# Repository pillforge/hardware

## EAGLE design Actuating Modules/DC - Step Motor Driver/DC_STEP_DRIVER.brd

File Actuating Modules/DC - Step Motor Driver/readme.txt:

XXXXXXXXXXXXXXXXXXXXXXXXXXXXXXXXXXXXXXXXXXXXXXXXXXXXXXXXXXXXXXXXXXXXXXXXXXXXX
X                                                                           X
X   Artwork and documentation done by: STORM LAB                            X
X                                                                           X
X   Company: VANDERBILT UNIVERSITY                                          X
XXXXXXXXXXXXXXXXXXXXXXXXXXXXXXXXXXXXXXXXXXXXXXXXXXXXXXXXXXXXXXXXXXXXXXXXXXXXX

PROJECT : DC_STEP_DRIVER
PCB NAME : DC_STEP_DRIVER
REVISION: 1.1 
DATE: 4-28-2015

PCB DESCRIPTION: 2 LAYER PCB 0.8 MM NOMINAL THICKNESS FR4
		Dimensions in mil (0.001 inch)
                            DOUBLE SIDE SOLDER MASK,
                            DOUBLE SIDE SILKSCREEN,
                            6 MIL MIN TRACE WIDTH AND 6 MIL MIN ISOLATION
		Dielectric constant for FR4 is 4.5

FILE NAME            		DESCRIPTION                               	FILE TYPE
-------------------------------------------------------------------------------------------
***PCB MANUFACTURING FILES:
DC_STEP_DRIVER.cmp				LAYER 1 COMPONENT SIDE/POSITIV              EXT. GERBER
DC_STEP_DRIVER.sol				LAYER 2 Inner layer/POSITIV                 EXT. GERBER

DC_STEP_DRIVER.stc				SOLDER MASK COMPONENT SIDE/NEGATIVE         EXT. GERBER
DC_STEP_DRIVER.stl				SOLDER MASK SOLDER SIDE/NEGATIVE            EXT. GERBER

DC_STEP_DRIVER.plc				SILKSCREEN COMPONENT SIDE/POSITIVE          EXT. GERBER
DC_STEP_DRIVER.pls				SILKSCREEN SOLDER SIDE/POSITIVE             EXT. GERBER

DC_STEP_DRIVER.crc				SOLDER PAST COMPONENT SIDE/POSITIVE         EXT. GERBER
DC_STEP_DRIVER.crs				SOLDER PAST SOLDER SIDE/POSITIVE            EXT. GERBER

DC_STEP_DRIVER.drd				DRILL/MECHANICAL DRAWING                    EXT. GERBER
DC_STEP_DRIVER.dri				DRILL/NC DRILL REPORT                       ASCII
DC_STEP_DRIVER.dim				BOARD OUTLINE                      	    EXT. GERBER

DC_STEP_DRIVER_partlist.xls		        PART LIST				    ASCII

***PDF FILES:
DC_STEP_DRIVER.PDF	Circuit Diagram

***EAGLE  FILES:
DC_STEP_DRIVER.SCH			Eagle 6.6 Schematic file
DC_STEP_DRIVER.BRD			Eagle 6.6 Layout file

README.TXT              THIS FILE                                   ASCII

***REVISION HISTORY

none

END.

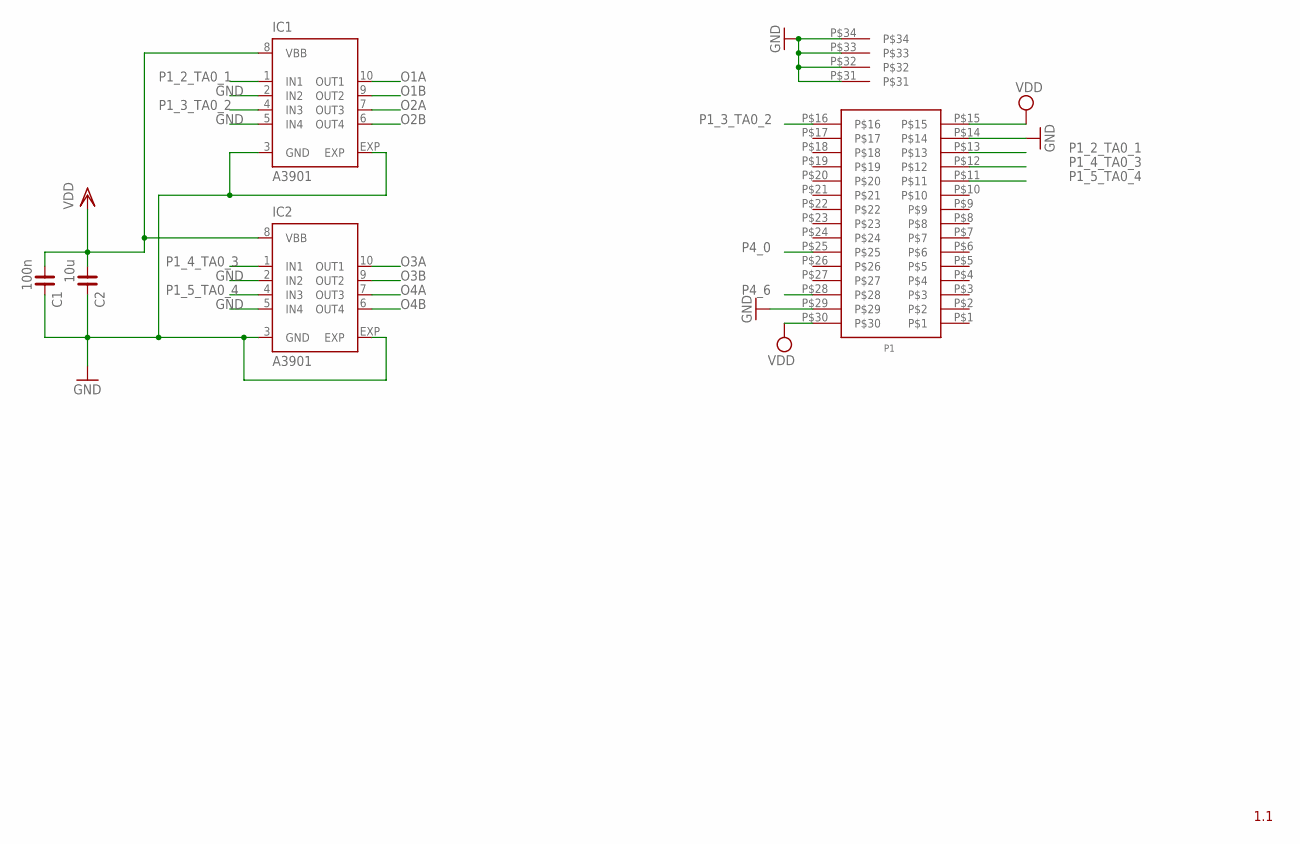
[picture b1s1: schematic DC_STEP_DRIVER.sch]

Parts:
C1: 100n; C0402
C2: 10u; C0402
IC1, IC2: A3901; DFN10-3X3
P1: 55909-0374; 55909-0374_PLUG

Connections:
GND: C1.2, C2.2, IC1.2 (IN2), IC1.3 (GND), IC1.5 (IN4), IC1.EXP, IC2.2 (IN2), IC2.3 (GND), IC2.5 (IN4), IC2.EXP, P1.P$14, P1.P$29, P1.P$31, P1.P$32, P1.P$33, P1.P$34
O1A: IC1.10 (OUT1)
O1B: IC1.9 (OUT2)
O2A: IC1.7 (OUT3)
O2B: IC1.6 (OUT4)
O3A: IC2.10 (OUT1)
O3B: IC2.9 (OUT2)
O4A: IC2.7 (OUT3)
O4B: IC2.6 (OUT4)
P1_2_TA0_1: IC1.1 (IN1), P1.P$13
P1_3_TA0_2: IC1.4 (IN3), P1.P$16
P1_4_TA0_3: IC2.1 (IN1), P1.P$12
P1_5_TA0_4: IC2.4 (IN3), P1.P$11
P4_0: P1.P$25
P4_6: P1.P$28
VDD: C1.1, C2.1, IC1.8 (VBB), IC2.8 (VBB), P1.P$15, P1.P$30

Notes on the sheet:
1.1

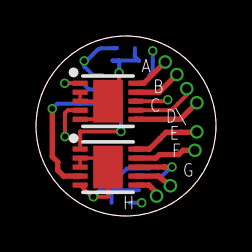
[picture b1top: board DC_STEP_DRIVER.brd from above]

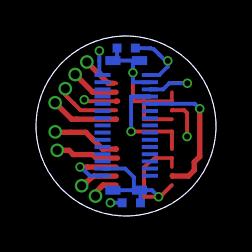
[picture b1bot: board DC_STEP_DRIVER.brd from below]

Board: 4 copper layers, 10.0 x 10.0 mm, 5 parts (3 on the bottom side), 6 nets.

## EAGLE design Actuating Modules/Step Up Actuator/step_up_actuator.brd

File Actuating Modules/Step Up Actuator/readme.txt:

XXXXXXXXXXXXXXXXXXXXXXXXXXXXXXXXXXXXXXXXXXXXXXXXXXXXXXXXXXXXXXXXXXXXXXXXXXXXX
X                                                                           X
X   Artwork and documentation done by: STORM LAB                            X
X                                                                           X
X   Company: VANDERBILT UNIVERSITY                                          X
XXXXXXXXXXXXXXXXXXXXXXXXXXXXXXXXXXXXXXXXXXXXXXXXXXXXXXXXXXXXXXXXXXXXXXXXXXXXX

PROJECT : step_up_actuator
PCB NAME : step_up_actuator
REVISION: 1.1 
DATE: 4-28-2015

PCB DESCRIPTION: 2 LAYER PCB 0.8 MM NOMINAL THICKNESS FR4
		Dimensions in mil (0.001 inch)
                            DOUBLE SIDE SOLDER MASK,
                            DOUBLE SIDE SILKSCREEN,
                            6 MIL MIN TRACE WIDTH AND 6 MIL MIN ISOLATION
		Dielectric constant for FR4 is 4.5

FILE NAME            		DESCRIPTION                               	FILE TYPE
-------------------------------------------------------------------------------------------
***PCB MANUFACTURING FILES:
step_up_actuator.cmp				LAYER 1 COMPONENT SIDE/POSITIV              EXT. GERBER
step_up_actuator.sol				LAYER 2 Inner layer/POSITIV                 EXT. GERBER

step_up_actuator.stc				SOLDER MASK COMPONENT SIDE/NEGATIVE         EXT. GERBER
step_up_actuator.stl				SOLDER MASK SOLDER SIDE/NEGATIVE            EXT. GERBER

step_up_actuator.plc				SILKSCREEN COMPONENT SIDE/POSITIVE          EXT. GERBER
step_up_actuator.pls				SILKSCREEN SOLDER SIDE/POSITIVE             EXT. GERBER

step_up_actuator.crc				SOLDER PAST COMPONENT SIDE/POSITIVE         EXT. GERBER
step_up_actuator.crs				SOLDER PAST SOLDER SIDE/POSITIVE            EXT. GERBER

step_up_actuator.drd				DRILL/MECHANICAL DRAWING                    EXT. GERBER
step_up_actuator.dri				DRILL/NC DRILL REPORT                       ASCII

step_up_actuator.dim				BOARD OUTLINE                      	    EXT. GERBER

step_up_actuator_partlist.xls		        PART LIST				    ASCII

***PDF FILES:
step_up_actuator.PDF	Circuit Diagram

***EAGLE  FILES:
step_up_actuator.SCH			Eagle 6.6 Schematic file
step_up_actuator.BRD			Eagle 6.6 Layout file

README.TXT              THIS FILE                                   ASCII

***REVISION HISTORY

none

END.

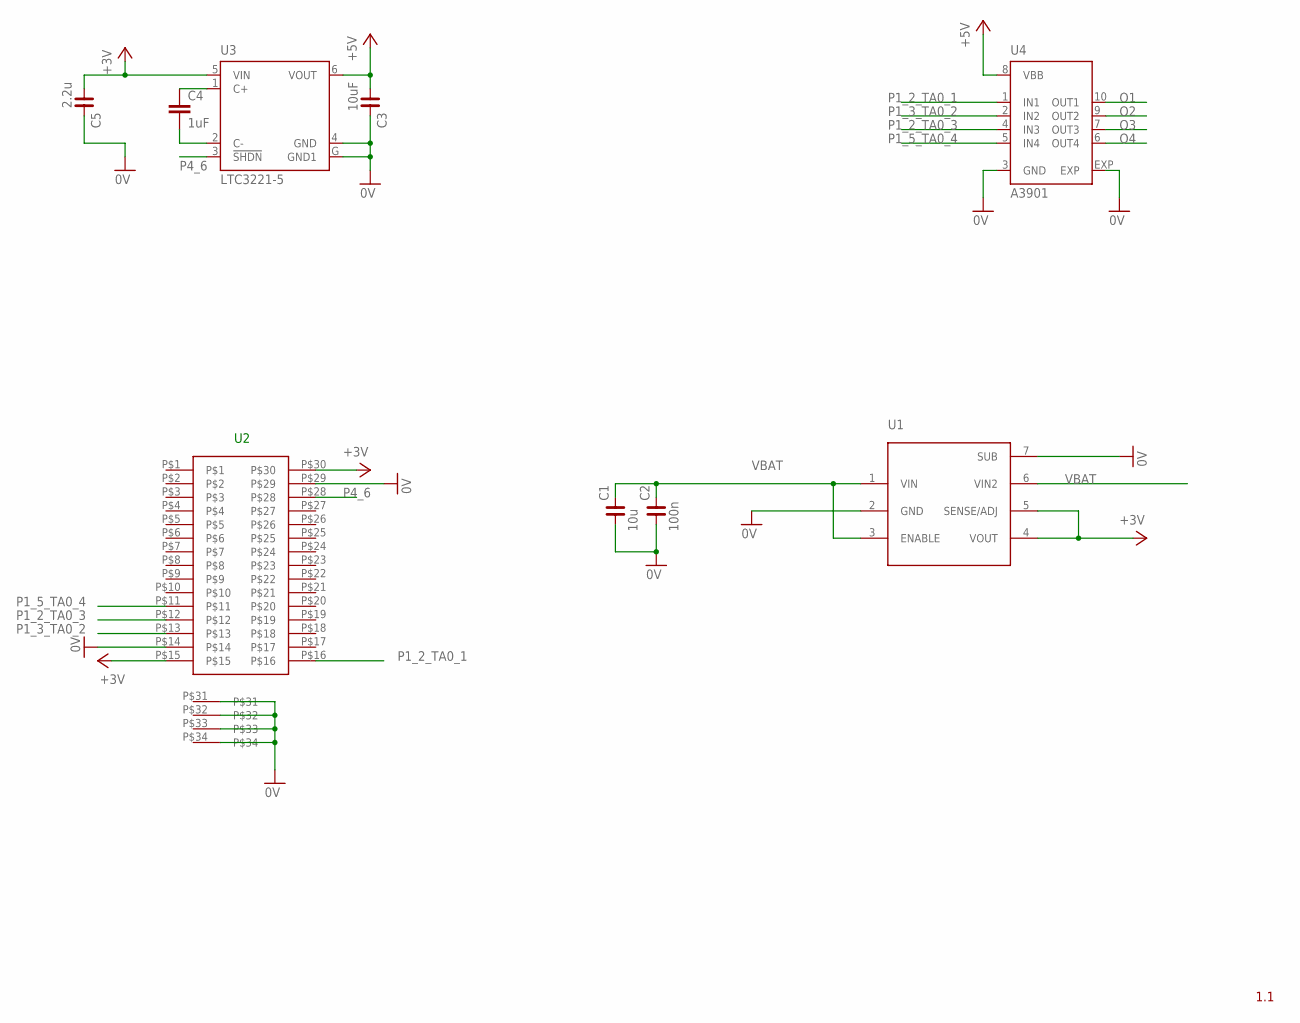
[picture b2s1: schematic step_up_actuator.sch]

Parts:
C1: 10u; C0402
C2: 100n; C0402
C3: 10uF; C1206
C4: 1uF; C0402
C5: 2.2u; C0402
U3: LTC3221-5; DFN6-2X2
U4: A3901; DFN10-3X3
U$1: NCP606
U$3: 51338-0374_RECEPTACLE

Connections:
0V: C1.1, C2.1, C3.2, C5.2, U3.4 (GND), U3.G (GND1), U4.3 (GND), U4.EXP, U$1.2 (GND), U$1.7 (SUB), U$3.P$14, U$3.P$29
+3V3: C5.1, U3.5 (VIN), U$1.4 (VOUT), U$1.5 (SENSE/ADJ), U$3.P$15, U$3.P$30
+5V: C3.1, U3.6 (VOUT), U4.8 (VBB)
unnamed: C4.1, U3.1 (C+)
unnamed: C4.2, U3.2 (C-)
O1: U4.10 (OUT1)
O2: U4.9 (OUT2)
O3: U4.7 (OUT3)
O4: U4.6 (OUT4)
P1_2_TA0_1: U4.1 (IN1), U$3.P$16
P1_2_TA0_3: U4.4 (IN3), U$3.P$12
P1_3_TA0_2: U4.2 (IN2), U$3.P$13
P1_5_TA0_4: U4.5 (IN4), U$3.P$11
P4_6: U3.3 (!SHDN), U$3.P$28
VBAT: C1.2, C2.2, U$1.1 (VIN), U$1.3 (ENABLE), U$1.6 (VIN2)

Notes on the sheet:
1.1

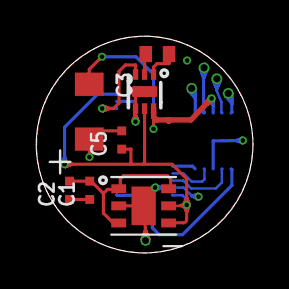
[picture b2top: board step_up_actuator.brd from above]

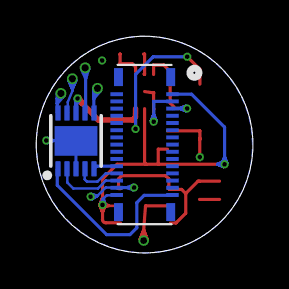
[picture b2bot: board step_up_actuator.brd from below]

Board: 4 copper layers, 12.0 x 12.0 mm, 9 parts (2 on the bottom side), 11 nets.

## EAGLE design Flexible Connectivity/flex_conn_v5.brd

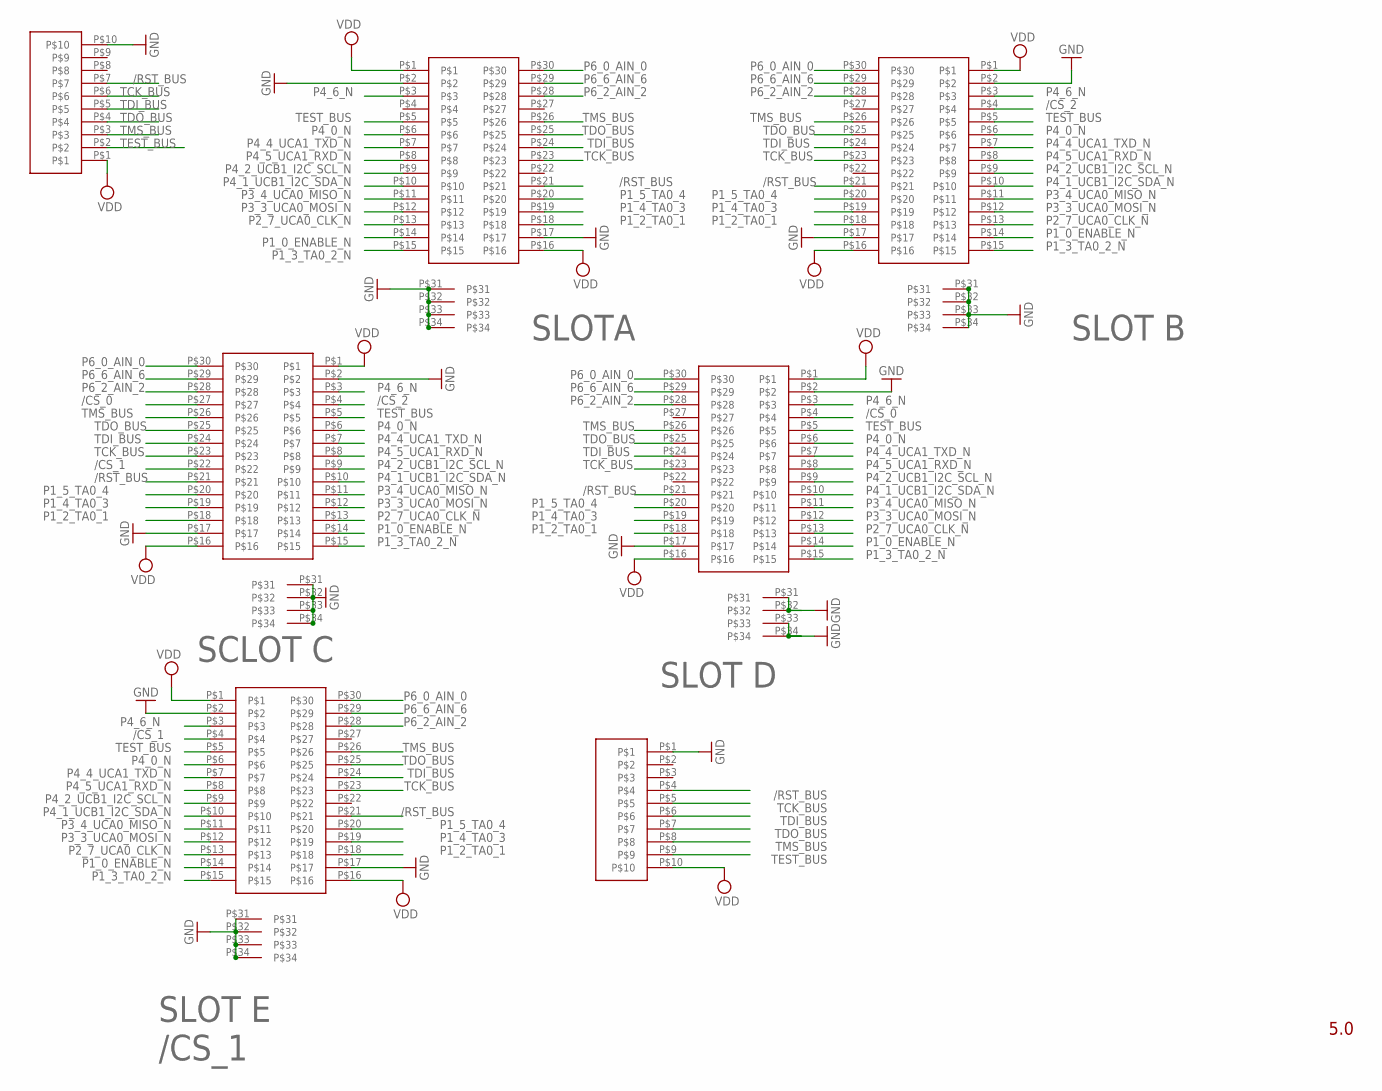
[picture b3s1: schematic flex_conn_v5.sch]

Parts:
U$1, U$2, U$3, U$4, U$6: 500913-0302_REC_30CONN_2
U$5, U$7: CABLE_ADAPTATOR; FPC_FFC

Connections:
/CS_0: U$1.P$4, U$6.P$27
/CS_1: U$4.P$4, U$6.P$22
/CS_2: U$2.P$4, U$6.P$4
/RST_BUS: U$1.P$21, U$2.P$21, U$3.P$21, U$4.P$21, U$5.P$7, U$6.P$21, U$7.P$4
GND: U$1.P$2, U$1.P$17, U$1.P$31, U$1.P$32, U$1.P$33, U$1.P$34, U$2.P$2, U$2.P$17, U$2.P$31, U$2.P$32, U$2.P$33, U$2.P$34, U$3.P$2, U$3.P$17, U$3.P$31, U$3.P$32, U$3.P$33, U$3.P$34, U$4.P$2, U$4.P$17, U$4.P$31, U$4.P$32, U$4.P$33, U$4.P$34, U$5.P$10, U$6.P$2, U$6.P$17, U$6.P$31, U$6.P$32, U$6.P$33, U$6.P$34, U$7.P$1
P1_0_ENABLE_N: U$1.P$14, U$2.P$14, U$3.P$14, U$4.P$14, U$6.P$14
P1_2_TA0_1: U$1.P$18, U$2.P$18, U$3.P$18, U$4.P$18, U$6.P$18
P1_3_TA0_2_N: U$1.P$15, U$2.P$15, U$3.P$15, U$4.P$15, U$6.P$15
P1_4_TA0_3: U$1.P$19, U$2.P$19, U$3.P$19, U$4.P$19, U$6.P$19
P1_5_TA0_4: U$1.P$20, U$2.P$20, U$3.P$20, U$4.P$20, U$6.P$20
P2_7_UCA0_CLK_N: U$1.P$13, U$2.P$13, U$3.P$13, U$4.P$13, U$6.P$13
P3_3_UCA0_MOSI_N: U$1.P$12, U$2.P$12, U$3.P$12, U$4.P$12, U$6.P$12
P3_4_UCA0_MISO_N: U$1.P$11, U$2.P$11, U$3.P$11, U$4.P$11, U$6.P$11
P4_0_N: U$1.P$6, U$2.P$6, U$3.P$6, U$4.P$6, U$6.P$6
P4_1_UCB1_I2C_SDA_N: U$1.P$10, U$2.P$10, U$3.P$10, U$4.P$10, U$6.P$10
P4_2_UCB1_I2C_SCL_N: U$1.P$9, U$2.P$9, U$3.P$9, U$4.P$9, U$6.P$9
P4_4_UCA1_TXD_N: U$1.P$7, U$2.P$7, U$3.P$7, U$4.P$7, U$6.P$7
P4_5_UCA1_RXD_N: U$1.P$8, U$2.P$8, U$3.P$8, U$4.P$8, U$6.P$8
P4_6_N: U$1.P$3, U$2.P$3, U$3.P$3, U$4.P$3, U$6.P$3
P6_0_AIN_0: U$1.P$30, U$2.P$30, U$3.P$30, U$4.P$30, U$6.P$30
P6_2_AIN_2: U$1.P$28, U$2.P$28, U$3.P$28, U$4.P$28, U$6.P$28
P6_6_AIN_6: U$1.P$29, U$2.P$29, U$3.P$29, U$4.P$29, U$6.P$29
TCK_BUS: U$1.P$23, U$2.P$23, U$3.P$23, U$4.P$23, U$5.P$6, U$6.P$23, U$7.P$5
TDI_BUS: U$1.P$24, U$2.P$24, U$3.P$24, U$4.P$24, U$5.P$5, U$6.P$24, U$7.P$6
TDO_BUS: U$1.P$25, U$2.P$25, U$3.P$25, U$4.P$25, U$5.P$4, U$6.P$25, U$7.P$7
TEST_BUS: U$1.P$5, U$2.P$5, U$3.P$5, U$4.P$5, U$5.P$2, U$6.P$5, U$7.P$9
TMS_BUS: U$1.P$26, U$2.P$26, U$3.P$26, U$4.P$26, U$5.P$3, U$6.P$26, U$7.P$8
VDD: U$1.P$1, U$1.P$16, U$2.P$1, U$2.P$16, U$3.P$1, U$3.P$16, U$4.P$1, U$4.P$16, U$5.P$1, U$6.P$1, U$6.P$16, U$7.P$10

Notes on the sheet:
SLOTA
SLOT B
SCLOT C
SLOT D
SLOT E
/CS_1
5.0

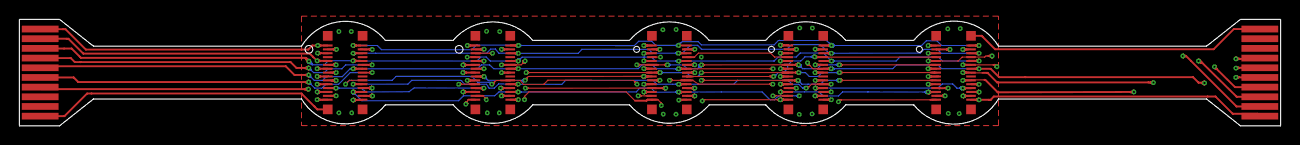
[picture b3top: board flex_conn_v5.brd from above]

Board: 4 copper layers, 130.3 x 11.0 mm, 7 parts (0 on the bottom side), 28 nets.

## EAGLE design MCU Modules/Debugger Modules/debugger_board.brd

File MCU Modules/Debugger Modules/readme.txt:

XXXXXXXXXXXXXXXXXXXXXXXXXXXXXXXXXXXXXXXXXXXXXXXXXXXXXXXXXXXXXXXXXXXXXXXXXXXXX
X                                                                           X
X   Artwork and documentation done by: STORM LAB                            X
X                                                                           X
X   Company: VANDERBILT UNIVERSITY                                          X
XXXXXXXXXXXXXXXXXXXXXXXXXXXXXXXXXXXXXXXXXXXXXXXXXXXXXXXXXXXXXXXXXXXXXXXXXXXXX

PROJECT : debugger_board
PCB NAME : debugger_board
REVISION: 1.1 
DATE: 4-28-2015

PCB DESCRIPTION: 2 LAYER PCB 0.8 MM NOMINAL THICKNESS FR4
		Dimensions in mil (0.001 inch)
                            DOUBLE SIDE SOLDER MASK,
                            DOUBLE SIDE SILKSCREEN,
                            6 MIL MIN TRACE WIDTH AND 6 MIL MIN ISOLATION
		Dielectric constant for FR4 is 4.5

FILE NAME            		DESCRIPTION                               	FILE TYPE
-------------------------------------------------------------------------------------------
***PCB MANUFACTURING FILES:
debugger_board.cmp				LAYER 1 COMPONENT SIDE/POSITIV              EXT. GERBER
debugger_board.sol				LAYER 2 Inner layer/POSITIV                 EXT. GERBER

debugger_board.stc				SOLDER MASK COMPONENT SIDE/NEGATIVE         EXT. GERBER
debugger_board.stl				SOLDER MASK SOLDER SIDE/NEGATIVE            EXT. GERBER

debugger_board.plc				SILKSCREEN COMPONENT SIDE/POSITIVE          EXT. GERBER
debugger_board.pls				SILKSCREEN SOLDER SIDE/POSITIVE             EXT. GERBER

debugger_board.crc				SOLDER PAST COMPONENT SIDE/POSITIVE         EXT. GERBER
debugger_board.crs				SOLDER PAST SOLDER SIDE/POSITIVE            EXT. GERBER

debugger_board.drd				DRILL/MECHANICAL DRAWING                    EXT. GERBER
debugger_board.dri				DRILL/NC DRILL REPORT                       ASCII

debugger_board.dim				BOARD OUTLINE                      	    EXT. GERBER

debugger_board_partlist.xls		        PART LIST				    ASCII

***PDF FILES:
debugger_board.PDF	Circuit Diagram

***EAGLE  FILES:
debugger_board.SCH			Eagle 6.6 Schematic file
debugger_board.BRD			Eagle 6.6 Layout file

README.TXT              THIS FILE                                   ASCII

***REVISION HISTORY

none

END.

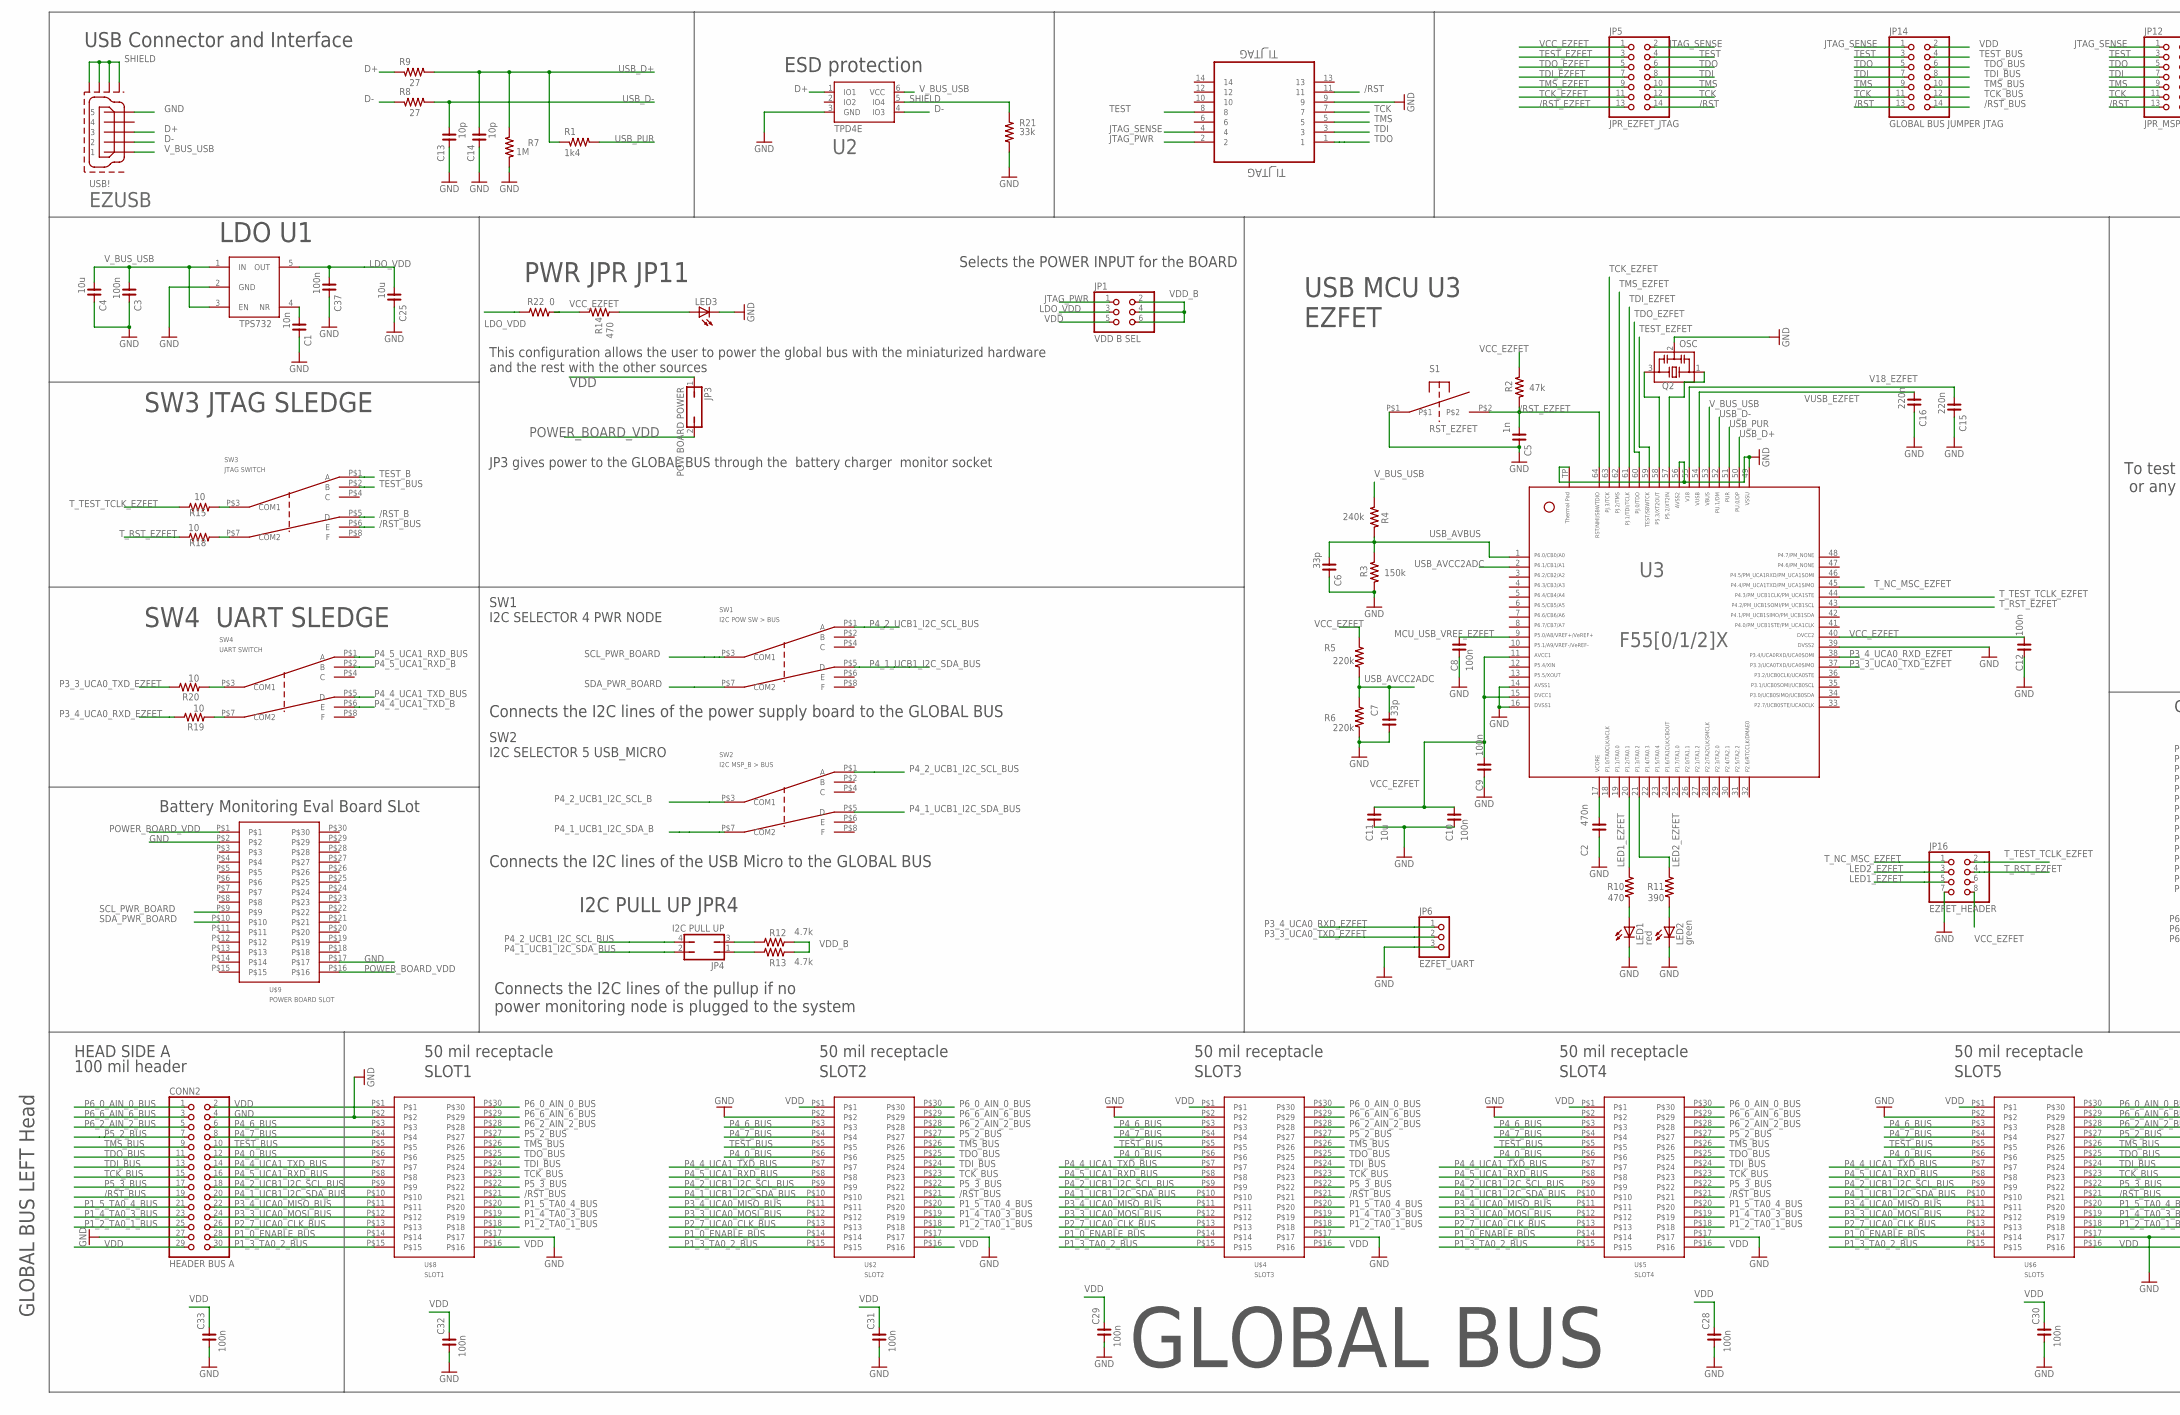
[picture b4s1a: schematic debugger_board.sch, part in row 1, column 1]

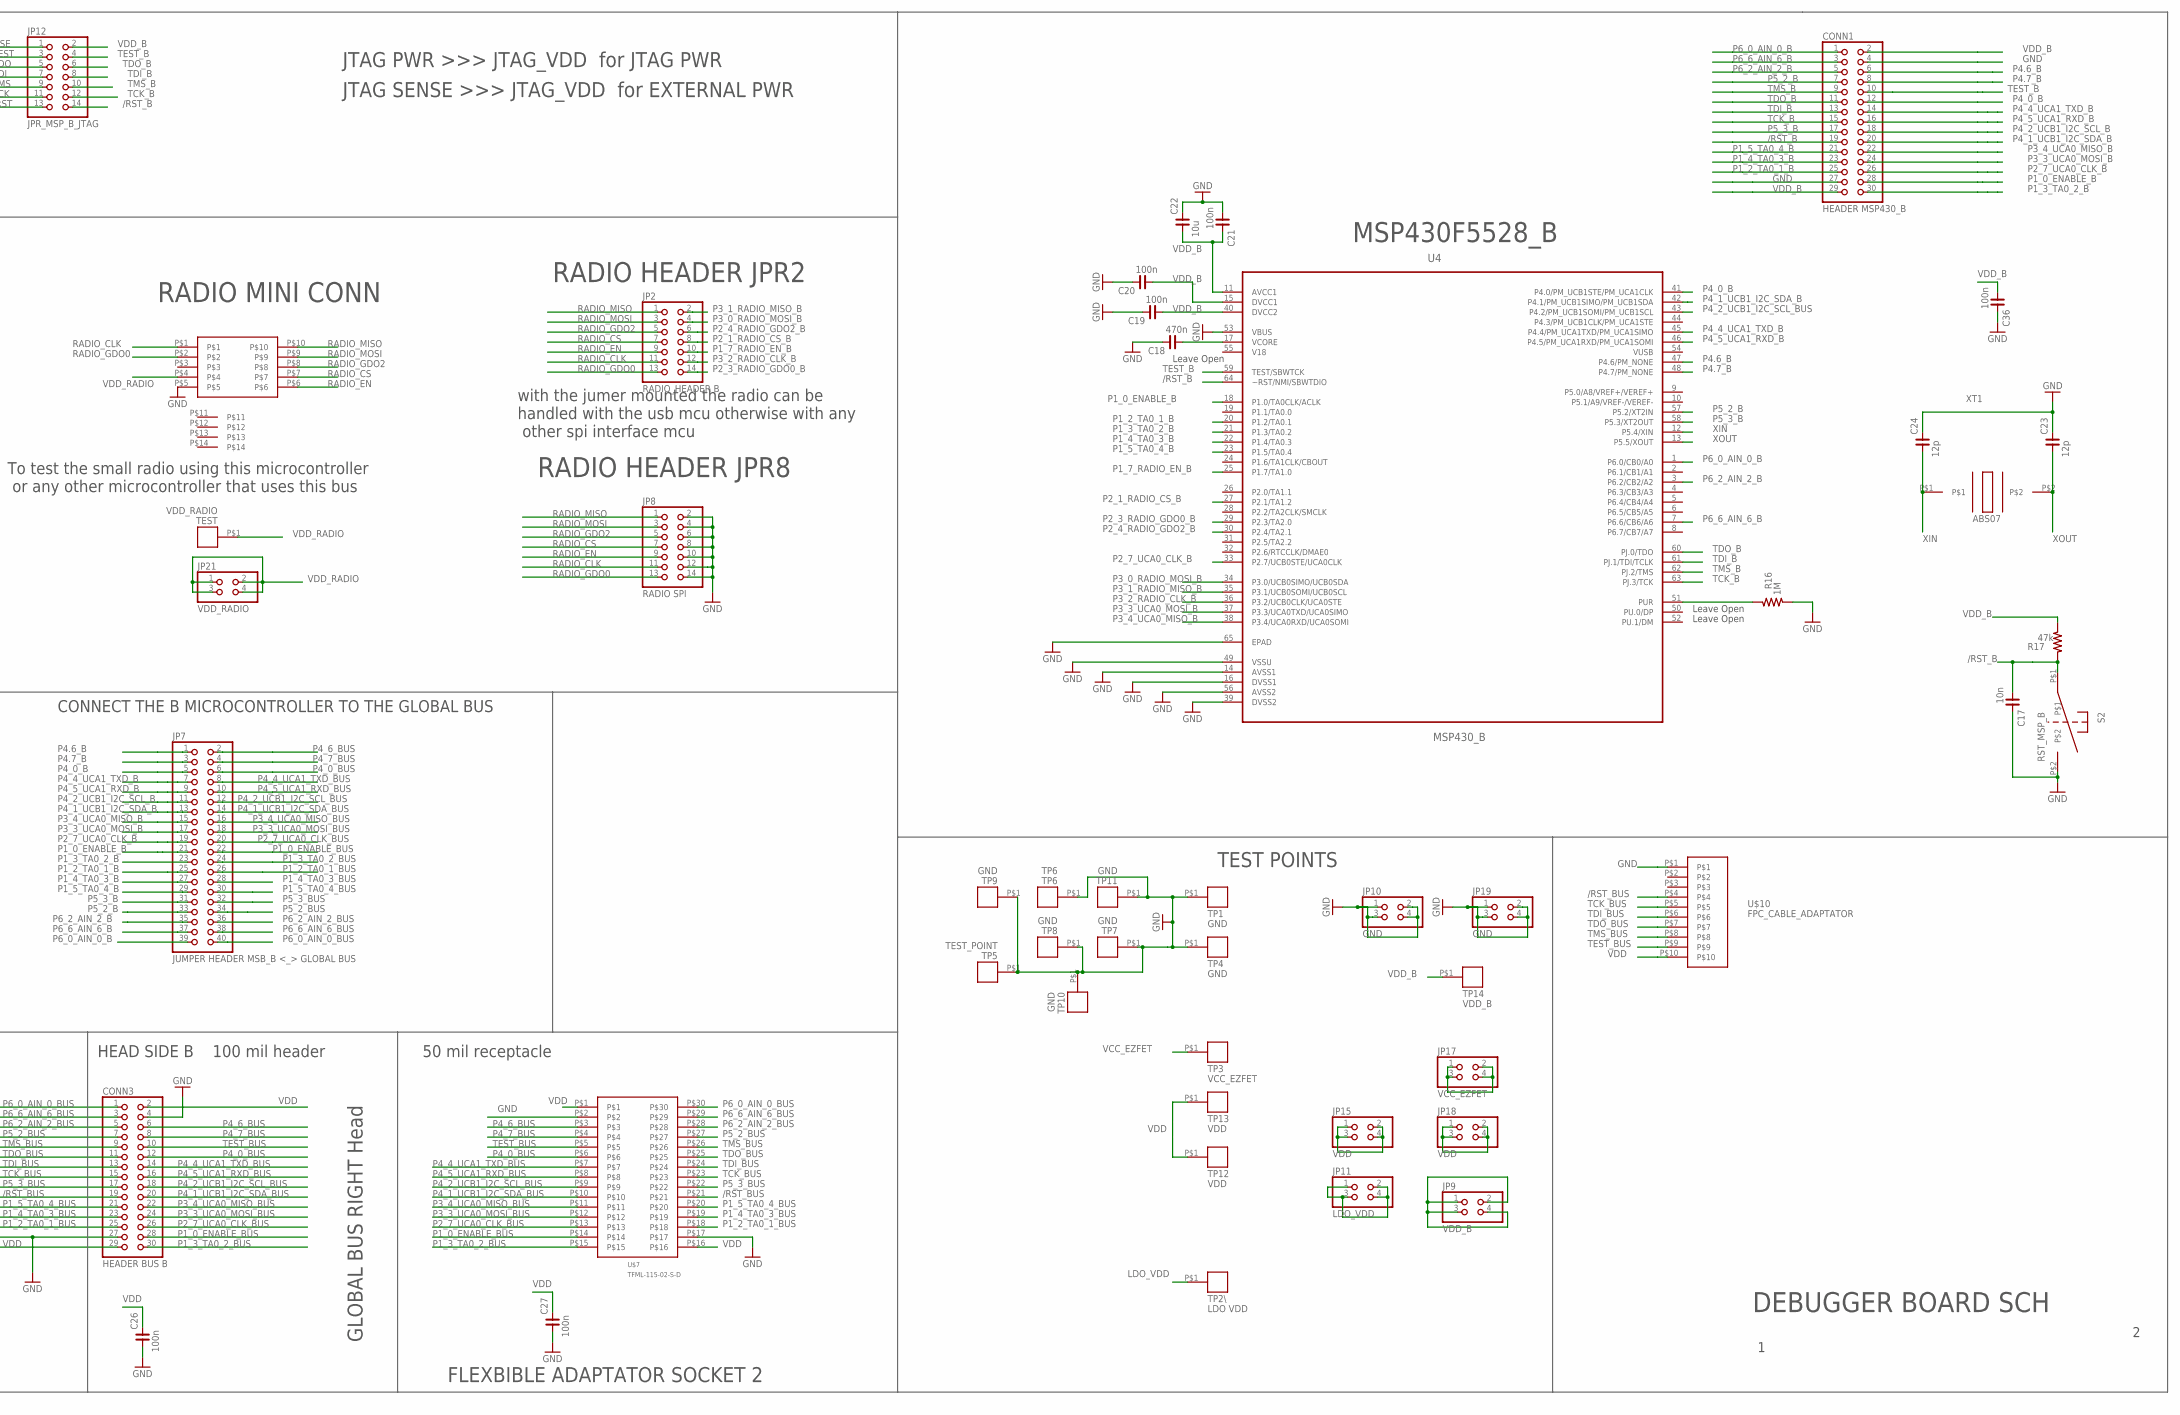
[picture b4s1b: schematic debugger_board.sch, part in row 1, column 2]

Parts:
C1, C17: 10n; C0603
C2, C18: 470n; C0603
C3, C8, C9, C10, C12, C19, C20, C21, C26, C27, C28, C29, C30, C31, C32, C33, C36, C37: 100n; C0603
C4, C11, C22, C25: 10u; C0603
C5: 1n; C0603
C6, C7: 33p; C0603
C13, C14: 10p; C0603
C15, C16: 220n; C0603
C23, C24: 12p; C0603
CONN1: HEADER MSP430_B; 2X15
CONN2: HEADER BUS A; 2X15
CONN3: HEADER BUS B; 2X15
EZUSB: USB!; UX60A-MB-5ST
JP1: VDD B SEL; 2X03
JP2: RADIO_HEADER B; 2X07
JP3: POW BOARD POWER; JP1
JP4: I2C PULL UP; JP2Q
JP5: JPR_EZFET_JTAG; 2X07
JP6: EZFET_UART; 1X03
JP7: JUMPER HEADER MSB_B <_> GLOBAL BUS; 2X20
JP8: RADIO SPI; 2X07
JP9: VDD_B; 2X02
JP10, JP19: GND; 2X02
JP11: LDO_VDD; 2X02
JP12: JPR_MSP_B_JTAG; 2X07
JP14: GLOBAL BUS JUMPER JTAG; 2X07
JP15, JP18: VDD; 2X02
JP16: EZFET_HEADER; 2X04
JP17: VCC_EZFET; 2X02
JP21: VDD_RADIO; 2X02
LED1: red; CHIP-LED0603
LED2: green; CHIP-LED0603
LED3: LEDCHIP-LED0603; CHIP-LED0603
Q2: OSC; CSTCR6M
R1: 1k4; R0603
R2, R17: 47k; R0603
R3: 150k; R0603
R4: 240k; R0603
R5, R6: 220k; R0603
R7, R16: 1M; R0603
R8, R9: 27; R0603
R10, R14: 470; R0603
R11: 390; R0603
R12, R13: 4.7k; R0603
R15, R18, R19, R20: 10; R0603
R21: 33k; R0603
R22: 0; R1206
RADIO_CONN: RADIO; 559099872_2X5_PLUG
S1: RST_EZFET; EVQ_11_TH
S2: RST_MSP_B; EVQ_11_TH
SW1: I2C POW SW > BUS; CL-SB-23B-02
SW2: I2C MSP_B > BUS; CL-SB-23B-02
SW3: JTAG SWITCH; CL-SB-23B-02
SW4: UART SWITCH; CL-SB-23B-02
TEST: VDD_RADIO; 5019_PAD
TI_JTAG: TI_JTAG; TYCO_5103308-2
TP1, TP4, TP7, TP8, TP9, TP10, TP11: GND; 5019_PAD
TP2\: LDO VDD; 5019_PAD
TP3: VCC_EZFET; 5019_PAD
TP5: TEST_POINT; 5019_PAD
TP6: TP6; 5019_PAD
TP12, TP13: VDD; 5019_PAD
TP14: VDD_B; 5019_PAD
U1: TPS73233; SOT23
U2: TPD4E; SON(DRY)6
U3: USB_EZFET; RGC64
U4: MSP430_B; QFN50P900X900X100-65N
U$2: SLOT2; TFML-115-02-S-D
U$4: SLOT3; TFML-115-02-S-D
U$5: SLOT4; TFML-115-02-S-D
U$6: SLOT5; TFML-115-02-S-D
U$7: TFML-115-02-S-D
U$8: SLOT1; TFML-115-02-S-D
U$9: POWER BOARD SLOT; TFML-115-02-S-D
U$10: FPC_CABLE_ADAPTATOR; FPC_FFC
U$16: OSC32K; ABS07

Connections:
/RST: JP5.14, JP12.13, JP14.13, TI_JTAG.11
/RST_B: C17.1, CONN1.19, JP12.14, R17.1, S2.P$1, SW3.P$5 (D), U4.64 (~RST/NMI/SBWTDIO)
/RST_BUS: CONN2.19, CONN3.19, JP14.14, SW3.P$6 (E), U$2.P$21, U$4.P$21, U$5.P$21, U$6.P$21, U$7.P$21, U$8.P$21, U$10.P$4
/RST_EZFET: C5.1, JP5.13, R2.1, S1.P$2, U3.64
D+: EZUSB.3, R9.1, U2.1 (IO1)
D-: EZUSB.2, R8.1, U2.4 (IO3)
GND: C1.2, C2.2, C3.2, C4.2, C5.2, C6.2, C7.1, C8.1, C9.1, C10.1, C11.1, C12.1, C13.2, C14.2, C15.2, C16.2, C17.2, C18.2, C19.2, C20.2, C21.1, C22.2, C23.2, C24.2, C25.2, C26.1, C27.1, C28.1, C29.1, C30.1, C31.1, C32.1, C33.1, C36.2, C37.2, CONN1.4, CONN1.27, CONN2.4, CONN2.27, CONN3.4, CONN3.27, EZUSB.5, JP6.3, JP8.2, JP8.4, JP8.6, JP8.8, JP8.10, JP8.12, JP8.14, JP10.1, JP10.2, JP10.3, JP10.4, JP16.7, JP19.1, JP19.2, JP19.3, JP19.4, LED1.C, LED2.C, LED3.C, Q2.2, R3.1, R6.2, R7.2, R16.2, R21.2, RADIO_CONN.P$5, S1.P$1, S2.P$2, TI_JTAG.9, TP1.P$1, TP4.P$1, TP5.P$1, TP6.P$1, TP7.P$1, TP8.P$1, TP9.P$1, TP10.P$1, TP11.P$1, U1.2 (GND), U2.3 (GND), U3.14, U3.16, U3.39, U3.49, U3.56, U3.TP, U4.14 (AVSS1), U4.16 (DVSS1), U4.39 (DVSS2), U4.49 (VSSU), U4.53 (VBUS), U4.56 (AVSS2), U4.65 (EPAD), U$2.P$2, U$2.P$17, U$4.P$2, U$4.P$17, U$5.P$2, U$5.P$17, U$6.P$2, U$6.P$17, U$7.P$2, U$7.P$17, U$8.P$2, U$8.P$17, U$9.P$2, U$9.P$17, U$10.P$1
JTAG_PWR: JP1.1, TI_JTAG.2
JTAG_SENSE: JP5.2, JP12.1, JP14.1, TI_JTAG.4
LDO_VDD: C25.1, C37.1, JP1.3, JP11.1, JP11.2, JP11.3, JP11.4, R22.2, TP2\.P$1, U1.5 (OUT)
LED1_EZFET: JP16.5, R10.2, U3.20
LED2_EZFET: JP16.3, R11.2, U3.21
MCU_USB_VREF_EZFET: C8.2, U3.9
unnamed: C18.1, U4.17 (VCORE)
unnamed: R16.1, U4.51 (PUR)
unnamed: JP4.1, R13.1
unnamed: C1.1, U1.4 (NR)
unnamed: Q2.3, U3.58
unnamed: Q2.1, U3.57
unnamed: C2.1, U3.17
unnamed: LED3.A, R14.1
unnamed: LED1.A, R10.1
unnamed: LED2.A, R11.1
unnamed: JP4.3, R12.1
unnamed: R15.1, SW3.P$3 (COM1)
unnamed: R18.2, SW3.P$7 (COM2)
unnamed: R20.1, SW4.P$3 (COM1)
unnamed: R19.1, SW4.P$7 (COM2)
P1_0_ENABLE_B: CONN1.28, JP7.21, U4.18 (P1.0/TA0CLK/ACLK)
P1_0_ENABLE_BUS: CONN2.28, CONN3.28, JP7.22, U$2.P$14, U$4.P$14, U$5.P$14, U$6.P$14, U$7.P$14, U$8.P$14
P1_2_TA0_1_B: CONN1.25, JP7.25, U4.20 (P1.2/TA0.1)
P1_2_TA0_1_BUS: CONN2.25, CONN3.25, JP7.26, U$2.P$18, U$4.P$18, U$5.P$18, U$6.P$18, U$7.P$18, U$8.P$18
P1_3_TA0_2_B: CONN1.30, JP7.23, U4.21 (P1.3/TA0.2)
P1_3_TA0_2_BUS: CONN2.30, CONN3.30, JP7.24, U$2.P$15, U$4.P$15, U$5.P$15, U$6.P$15, U$7.P$15, U$8.P$15
P1_4_TA0_3_B: CONN1.23, JP7.27, U4.22 (P1.4/TA0.3)
P1_4_TA0_3_BUS: CONN2.23, CONN3.23, JP7.28, U$2.P$19, U$4.P$19, U$5.P$19, U$6.P$19, U$7.P$19, U$8.P$19
P1_5_TA0_4_B: CONN1.21, JP7.29, U4.23 (P1.5/TA0.4)
P1_5_TA0_4_BUS: CONN2.21, CONN3.21, JP7.30, U$2.P$20, U$4.P$20, U$5.P$20, U$6.P$20, U$7.P$20, U$8.P$20
P1_7_RADIO_EN_B: JP2.10, U4.25 (P1.7/TA1.0)
P2_1_RADIO_CS_B: JP2.8, U4.27 (P2.1/TA1.2)
P2_3_RADIO_GDO0_B: JP2.14, U4.29 (P2.3/TA2.0)
P2_4_RADIO_GDO2_B: JP2.6, U4.30 (P2.4/TA2.1)
P2_7_UCA0_CLK_B: CONN1.26, JP7.19, U4.33 (P2.7/UCB0STE/UCA0CLK)
P2_7_UCA0_CLK_BUS: CONN2.26, CONN3.26, JP7.20, U$2.P$13, U$4.P$13, U$5.P$13, U$6.P$13, U$7.P$13, U$8.P$13
P3_0_RADIO_MOSI_B: JP2.4, U4.34 (P3.0/UCB0SIMO/UCB0SDA)
P3_1_RADIO_MISO_B: JP2.2, U4.35 (P3.1/UCB0SOMI/UCB0SCL)
P3_2_RADIO_CLK_B: JP2.12, U4.36 (P3.2/UCB0CLK/UCA0STE)
P3_3_UCA0_MOSI_B: CONN1.24, JP7.17, U4.37 (P3.3/UCA0TXD/UCA0SIMO)
P3_3_UCA0_MOSI_BUS: CONN2.24, CONN3.24, JP7.18, U$2.P$12, U$4.P$12, U$5.P$12, U$6.P$12, U$7.P$12, U$8.P$12
P3_3_UCA0_TXD_EZFET: JP6.2, R20.2, U3.37
P3_4_UCA0_MISO_B: CONN1.22, JP7.15, U4.38 (P3.4/UCA0RXD/UCA0SOMI)
P3_4_UCA0_MISO_BUS: CONN2.22, CONN3.22, JP7.16, U$2.P$11, U$4.P$11, U$5.P$11, U$6.P$11, U$7.P$11, U$8.P$11
P3_4_UCA0_RXD_EZFET: JP6.1, R19.2, U3.38
P4.6_B: CONN1.6, JP7.1, U4.47 (P4.6/PM_NONE)
P4.7_B: CONN1.8, JP7.3, U4.48 (P4.7/PM_NONE)
P4_0_B: CONN1.12, JP7.5, U4.41 (P4.0/PM_UCB1STE/PM_UCA1CLK)
P4_0_BUS: CONN2.12, CONN3.12, JP7.6, U$2.P$6, U$4.P$6, U$5.P$6, U$6.P$6, U$7.P$6, U$8.P$6
P4_1_UCB1_I2C_SDA_B: CONN1.20, JP7.13, SW2.P$7 (COM2), U4.42 (P4.1/PM_UCB1SIMO/PM_UCB1SDA)
P4_1_UCB1_I2C_SDA_BUS: CONN2.20, CONN3.20, JP4.2, JP7.14, SW1.P$5 (D), SW2.P$5 (D), U$2.P$10, U$4.P$10, U$5.P$10, U$6.P$10, U$7.P$10, U$8.P$10
P4_2_UCB1_I2C_SCL_B: CONN1.18, JP7.11, SW2.P$3 (COM1)
P4_2_UCB1_I2C_SCL_BUS: CONN2.18, CONN3.18, JP4.4, JP7.12, SW1.P$1 (A), SW2.P$1 (A), U4.43 (P4.2/PM_UCB1SOMI/PM_UCB1SCL), U$2.P$9, U$4.P$9, U$5.P$9, U$6.P$9, U$7.P$9, U$8.P$9
P4_4_UCA1_TXD_B: CONN1.14, JP7.7, SW4.P$6 (E), U4.45 (P4.4/PM_UCA1TXD/PM_UCA1SIMO)
P4_4_UCA1_TXD_BUS: CONN2.14, CONN3.14, JP7.8, SW4.P$5 (D), U$2.P$7, U$4.P$7, U$5.P$7, U$6.P$7, U$7.P$7, U$8.P$7
P4_5_UCA1_RXD_B: CONN1.16, JP7.9, SW4.P$2 (B), U4.46 (P4.5/PM_UCA1RXD/PM_UCA1SOMI)
P4_5_UCA1_RXD_BUS: CONN2.16, CONN3.16, JP7.10, SW4.P$1 (A), U$2.P$8, U$4.P$8, U$5.P$8, U$6.P$8, U$7.P$8, U$8.P$8
P4_6_BUS: CONN2.6, CONN3.6, JP7.2, U$2.P$3, U$4.P$3, U$5.P$3, U$6.P$3, U$7.P$3, U$8.P$3
P4_7_BUS: CONN2.8, CONN3.8, JP7.4, U$2.P$4, U$4.P$4, U$5.P$4, U$6.P$4, U$7.P$4, U$8.P$4
P5_2_B: CONN1.7, JP7.33, U4.57 (P5.2/XT2IN)
P5_2_BUS: CONN2.7, CONN3.7, JP7.34, U$2.P$27, U$4.P$27, U$5.P$27, U$6.P$27, U$7.P$27, U$8.P$27
P5_3_B: CONN1.17, JP7.31, U4.58 (P5.3/XT2OUT)
P5_3_BUS: CONN2.17, CONN3.17, JP7.32, U$2.P$22, U$4.P$22, U$5.P$22, U$6.P$22, U$7.P$22, U$8.P$22
P6_0_AIN_0_B: CONN1.1, JP7.39, U4.1 (P6.0/CB0/A0)
P6_0_AIN_0_BUS: CONN2.1, CONN3.1, JP7.40, U$2.P$30, U$4.P$30, U$5.P$30, U$6.P$30, U$7.P$30, U$8.P$30
P6_2_AIN_2_B: CONN1.5, JP7.35, U4.3 (P6.2/CB2/A2)
P6_2_AIN_2_BUS: CONN2.5, CONN3.5, JP7.36, U$2.P$28, U$4.P$28, U$5.P$28, U$6.P$28, U$7.P$28, U$8.P$28
P6_6_AIN_6_B: CONN1.3, JP7.37, U4.7 (P6.6/CB6/A6)
P6_6_AIN_6_BUS: CONN2.3, CONN3.3, JP7.38, U$2.P$29, U$4.P$29, U$5.P$29, U$6.P$29, U$7.P$29, U$8.P$29
POWER_BOARD_VDD: JP3.2, U$9.P$1, U$9.P$16
RADIO_CLK: JP2.11, JP8.11, RADIO_CONN.P$1
RADIO_CS: JP2.7, JP8.7, RADIO_CONN.P$7
RADIO_EN: JP2.9, JP8.9, RADIO_CONN.P$6
RADIO_GDO0: JP2.13, JP8.13, RADIO_CONN.P$2
RADIO_GDO2: JP2.5, JP8.5, RADIO_CONN.P$8
RADIO_MISO: JP2.1, JP8.1, RADIO_CONN.P$10
RADIO_MOSI: JP2.3, JP8.3, RADIO_CONN.P$9
SCL_PWR_BOARD: SW1.P$3 (COM1), U$9.P$9
SDA_PWR_BOARD: SW1.P$7 (COM2), U$9.P$10
SHIELD: EZUSB.M1 (GND1), EZUSB.M2 (GND2), EZUSB.M3 (GND3), EZUSB.M4 (GND4), R21.1, U2.5 (IO4)
TCK: JP5.12, JP12.11, JP14.11, TI_JTAG.7
TCK_B: CONN1.15, JP12.12, U4.63 (PJ.3/TCK)
TCK_BUS: CONN2.15, CONN3.15, JP14.12, U$2.P$23, U$4.P$23, U$5.P$23, U$6.P$23, U$7.P$23, U$8.P$23, U$10.P$5
TCK_EZFET: JP5.11, U3.63
TDI: JP5.8, JP12.7, JP14.7, TI_JTAG.3
TDI_B: CONN1.13, JP12.8, U4.61 (PJ.1/TDI/TCLK)
TDI_BUS: CONN2.13, CONN3.13, JP14.8, U$2.P$24, U$4.P$24, U$5.P$24, U$6.P$24, U$7.P$24, U$8.P$24, U$10.P$6
TDI_EZFET: JP5.7, U3.61
TDO: JP5.6, JP12.5, JP14.5, TI_JTAG.1
TDO_B: CONN1.11, JP12.6, U4.60 (PJ.0/TDO)
TDO_BUS: CONN2.11, CONN3.11, JP14.6, U$2.P$25, U$4.P$25, U$5.P$25, U$6.P$25, U$7.P$25, U$8.P$25, U$10.P$7
TDO_EZFET: JP5.5, U3.60
TEST: JP5.4, JP12.3, JP14.3, TI_JTAG.8
TEST_B: CONN1.10, JP12.4, SW3.P$1 (A), U4.59 (TEST/SBWTCK)
TEST_BUS: CONN2.10, CONN3.10, JP14.4, SW3.P$2 (B), U$2.P$5, U$4.P$5, U$5.P$5, U$6.P$5, U$7.P$5, U$8.P$5, U$10.P$9
TEST_EZFET: JP5.3, U3.59
TMS: JP5.10, JP12.9, JP14.9, TI_JTAG.5
TMS_B: CONN1.9, JP12.10, U4.62 (PJ.2/TMS)
TMS_BUS: CONN2.9, CONN3.9, JP14.10, U$2.P$26, U$4.P$26, U$5.P$26, U$6.P$26, U$7.P$26, U$8.P$26, U$10.P$8
TMS_EZFET: JP5.9, U3.62
T_NC_MSC_EZFET: JP16.1, U3.45
T_RST_EZFET: JP16.4, R18.1, U3.43
T_TEST_TCLK_EZFET: JP16.2, R15.2, U3.44
USB_AVBUS: C6.1, R3.2, R4.2, U3.1
USB_AVCC2ADC: C7.2, R5.2, R6.1, U3.2
USB_D+: C14.1, R1.1, R7.1, R9.2, U3.50
USB_D-: C13.1, R8.2, U3.52
USB_PUR: R1.2, U3.51
V18: U4.55 (V18)
V18_EZFET: C15.1, U3.55
VCC_EZFET: C9.2, C10.2, C11.2, C12.2, JP5.1, JP16.8, JP17.1, JP17.2, JP17.3, JP17.4, R2.2, R5.1, R14.2, R22.1, TP3.P$1, U3.11, U3.15, U3.40
VDD: C26.2, C27.2, C28.2, C29.2, C30.2, C31.2, C32.2, C33.2, CONN2.2, CONN2.29, CONN3.2, CONN3.29, JP1.5, JP3.1, JP14.2, JP15.1, JP15.2, JP15.3, JP15.4, JP18.1, JP18.2, JP18.3, JP18.4, TP12.P$1, TP13.P$1, U$2.P$1, U$2.P$16, U$4.P$1, U$4.P$16, U$5.P$1, U$5.P$16, U$6.P$1, U$6.P$16, U$7.P$1, U$7.P$16, U$8.P$1, U$8.P$16, U$10.P$10
VDD_B: C19.1, C20.1, C21.2, C22.1, C36.1, CONN1.2, CONN1.29, JP1.2, JP1.4, JP1.6, JP9.1, JP9.2, JP9.3, JP9.4, JP12.2, R12.2, R13.2, R17.2, TP14.P$1, U4.11 (AVCC1), U4.15 (DVCC1), U4.40 (DVCC2)
VDD_RADIO: JP21.1, JP21.2, JP21.3, JP21.4, RADIO_CONN.P$4, TEST.P$1
VUSB_EZFET: C16.1, U3.54
V_BUS_USB: C3.1, C4.1, EZUSB.1, R4.1, U1.1 (IN), U1.3 (EN), U2.6 (VCC), U3.53
XIN: C24.1, U4.12 (P5.4/XIN), U$16.P$1
XOUT: C23.1, U4.13 (P5.5/XOUT), U$16.P$2

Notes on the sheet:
USB Connector and Interface
ESD protection
LDO U1
SW1 I2C SELECTOR 4 PWR NODE
Connects the I2C lines of the power supply board to the GLOBAL BUS
FLEXBIBLE ADAPTATOR SOCKET 2
SW3 JTAG SLEDGE
Connects the I2C lines of the USB Micro to the GLOBAL BUS
100 mil header
SW2 I2C SELECTOR 5 USB_MICRO
I2C PULL UP JPR4
50 mil receptacle
Battery Monitoring Eval Board SLot
PWR JPR JP11
Selects the POWER INPUT for the BOARD
Connects the I2C lines of the pullup if no power monitoring node is plugged to the system
HEAD SIDE A
RADIO MINI CONN
To test the small radio using this microcontroller or any other microcontroller that uses this bus
RADIO HEADER JPR2
with the jumer mounted the radio can be handled with the usb mcu otherwise with any other spi interface mcu
USB MCU U3 EZFET
GLOBAL BUS
GLOBAL BUS LEFT Head
GLOBAL BUS RIGHT Head
This configuration allows the user to power the global bus with the miniaturized hardware and the rest with the other sources
JP3 gives power to the GLOBAL BUS through the battery charger monitor socket
Leave Open
MSP430F5528_B
RADIO HEADER JPR8
XT1
JTAG SENSE >>> JTAG_VDD for EXTERNAL PWR
JTAG PWR >>> JTAG_VDD for JTAG PWR
CONNECT THE B MICROCONTROLLER TO THE GLOBAL BUS
TEST POINTS
SW4 UART SLEDGE
DEBUGGER BOARD SCH
HEAD SIDE B
SLOT5
SLOT4

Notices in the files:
parts and their libraries:
rc-master-smd: Copyright (C) 2007, Bob Starr
